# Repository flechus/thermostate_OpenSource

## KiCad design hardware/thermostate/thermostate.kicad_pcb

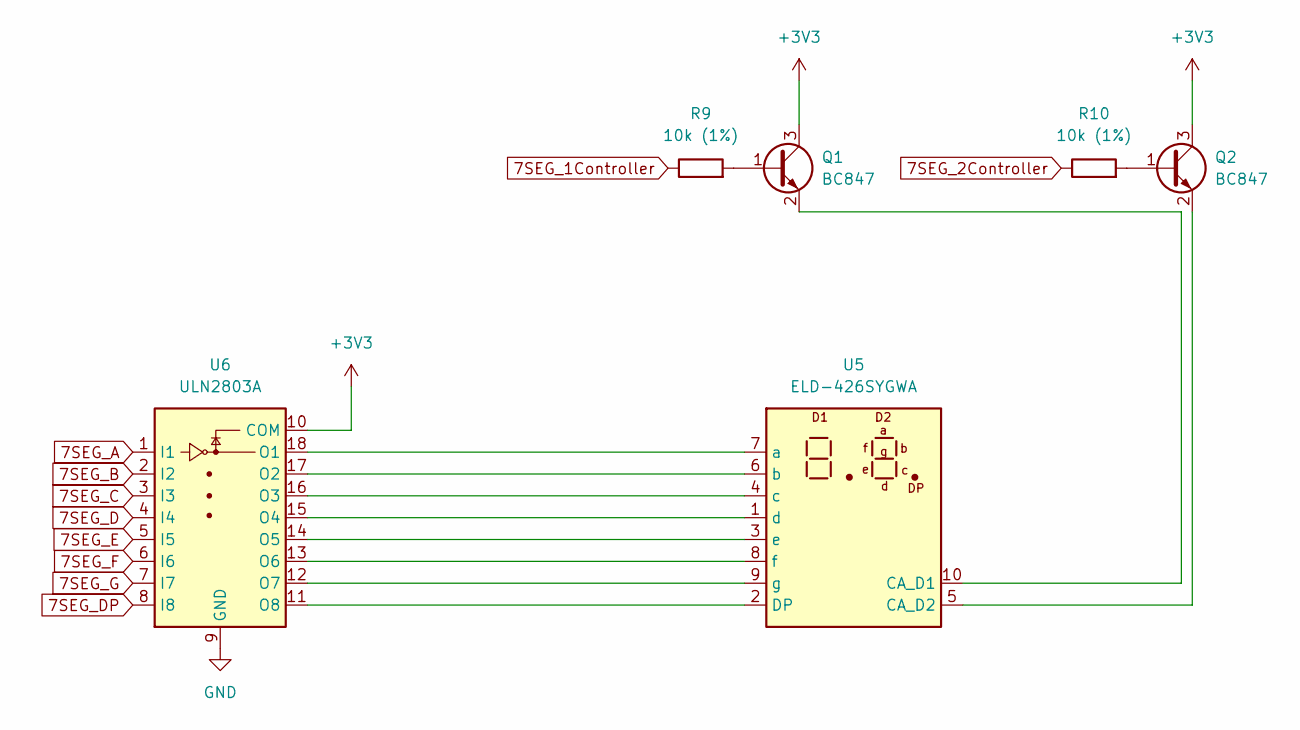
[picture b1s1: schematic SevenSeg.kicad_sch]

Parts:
Q1, Q2: BC847; SOT-23; LCSC Part# C181140
R9, R10: 10k (1%); R_0805_2012Metric_Pad1.20x1.40mm_HandSolder; LCSC Part# C17414
U5: ELD-426SYGWA; ELD_426XXXX
U6: ULN2803A; QFN-20-1EP_4x4mm_P0.5mm_EP2.5x2.5mm; LCSC Part# C493377

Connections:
7SEG_1Controller: R9.1; also elsewhere on the board
7SEG_2Controller: R10.1; also elsewhere on the board
7SEG_A: U6.1 (I1); also elsewhere on the board
7SEG_B: U6.2 (I2); also elsewhere on the board
7SEG_C: U6.3 (I3); also elsewhere on the board
7SEG_D: U6.4 (I4); also elsewhere on the board
7SEG_DP: U6.8 (I8); also elsewhere on the board
7SEG_E: U6.5 (I5); also elsewhere on the board
7SEG_F: U6.6 (I6); also elsewhere on the board
7SEG_G: U6.7 (I7); also elsewhere on the board
ESP_3V3: Q1.3 (C), Q2.3 (C), U6.10 (COM); also elsewhere on the board
GND: U6.9 (GND); also elsewhere on the board
unnamed: Q1.1 (B), R9.2
unnamed: Q1.2 (E), U5.10 (CA_D1)
unnamed: Q2.1 (B), R10.2
unnamed: Q2.2 (E), U5.5 (CA_D2)
unnamed: U5.1 (d), U6.15 (O4)
unnamed: U5.2 (DP), U6.11 (O8)
unnamed: U5.3 (e), U6.14 (O5)
unnamed: U5.4 (c), U6.16 (O3)
unnamed: U5.6 (b), U6.17 (O2)
unnamed: U5.7 (a), U6.18 (O1)
unnamed: U5.8 (f), U6.13 (O6)
unnamed: U5.9 (g), U6.12 (O7)

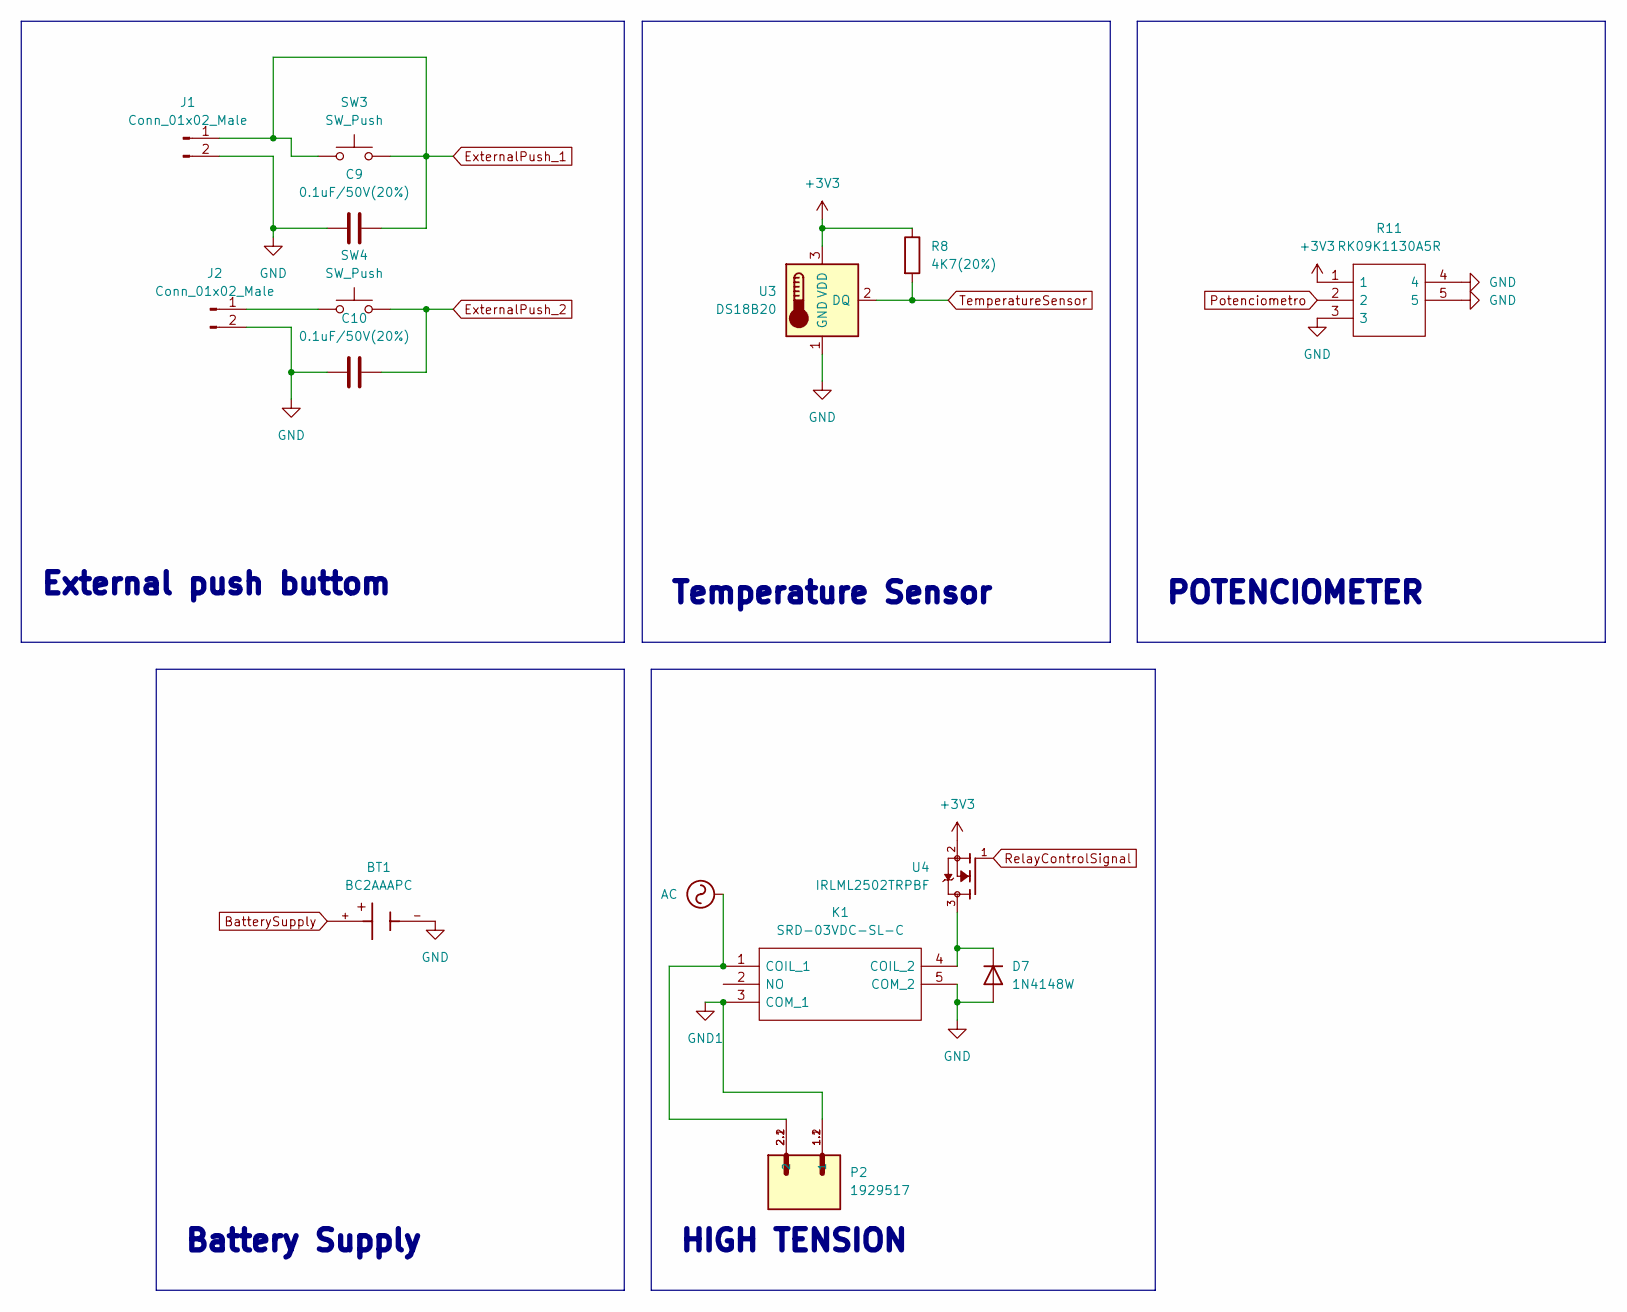
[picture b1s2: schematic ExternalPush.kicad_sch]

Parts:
BT1: BC2AAAPC; BAT_BC2AAAPC; PARTREV L
C9, C10: 0.1uF/50V(20%); C_0805_2012Metric_Pad1.18x1.45mm_HandSolder; LCSC Part# C138340
D7: 1N4148W; D_SOD-123
J1, J2: Conn_01x02_Male; TerminalBlock_MetzConnect_360291_1x01_Horizontal_ScrewM3.0_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
K1: SRD-03VDC-SL-C; SRD03VDCSLC; Manufacturer_Part_Number SRD-03VDC-SL-C; LCSC Part# C24585
P2: 1929517; PHOENIX_1929517
R8: 4K7(20%); R_0805_2012Metric_Pad1.20x1.40mm_HandSolder
R11: RK09K1130A5R; Manufacturer_Part_Number RK09K1130A5R; Mouser Part Number 688-RK09K1130A5R
SW3, SW4: SW_Push; SW_Push_1P1T_NO_CK_KMR2
U3: DS18B20; TO-92_Inline; LCSC Part# C9753
U4: IRLML2502TRPBF; SOT-23; LCSC Part# C2589

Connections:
AC: K1.1 (COIL_1), P2.2.1 (2), P2.2.2 (2)
BatterySupply: BT1.+; also elsewhere on the board
ESP_3V3: R8.1, R11.1, U3.3 (VDD), U4.2; also elsewhere on the board
ExternalPush_1: C9.2, J1.1, SW3.1, SW3.2; also elsewhere on the board
ExternalPush_2: C10.2, SW4.2; also elsewhere on the board
GND: BT1.-, C9.1, C10.1, D7.2 (A), J1.2, J2.2, K1.5 (COM_2), R11.3, R11.4, R11.5, U3.1 (GND); also elsewhere on the board
GND1: K1.3 (COM_1), P2.1.1 (1), P2.1.2 (1)
unnamed: D7.1 (K), K1.4 (COIL_2), U4.3
unnamed: J2.1, SW4.1
Potenciometro: R11.2; also elsewhere on the board
RelayControlSignal: U4.1; also elsewhere on the board
TemperatureSensor: R8.2, U3.2 (DQ); also elsewhere on the board

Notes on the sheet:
Battery Supply
POTENCIOMETER
HIGH TENSION
Temperature Sensor
External push buttom

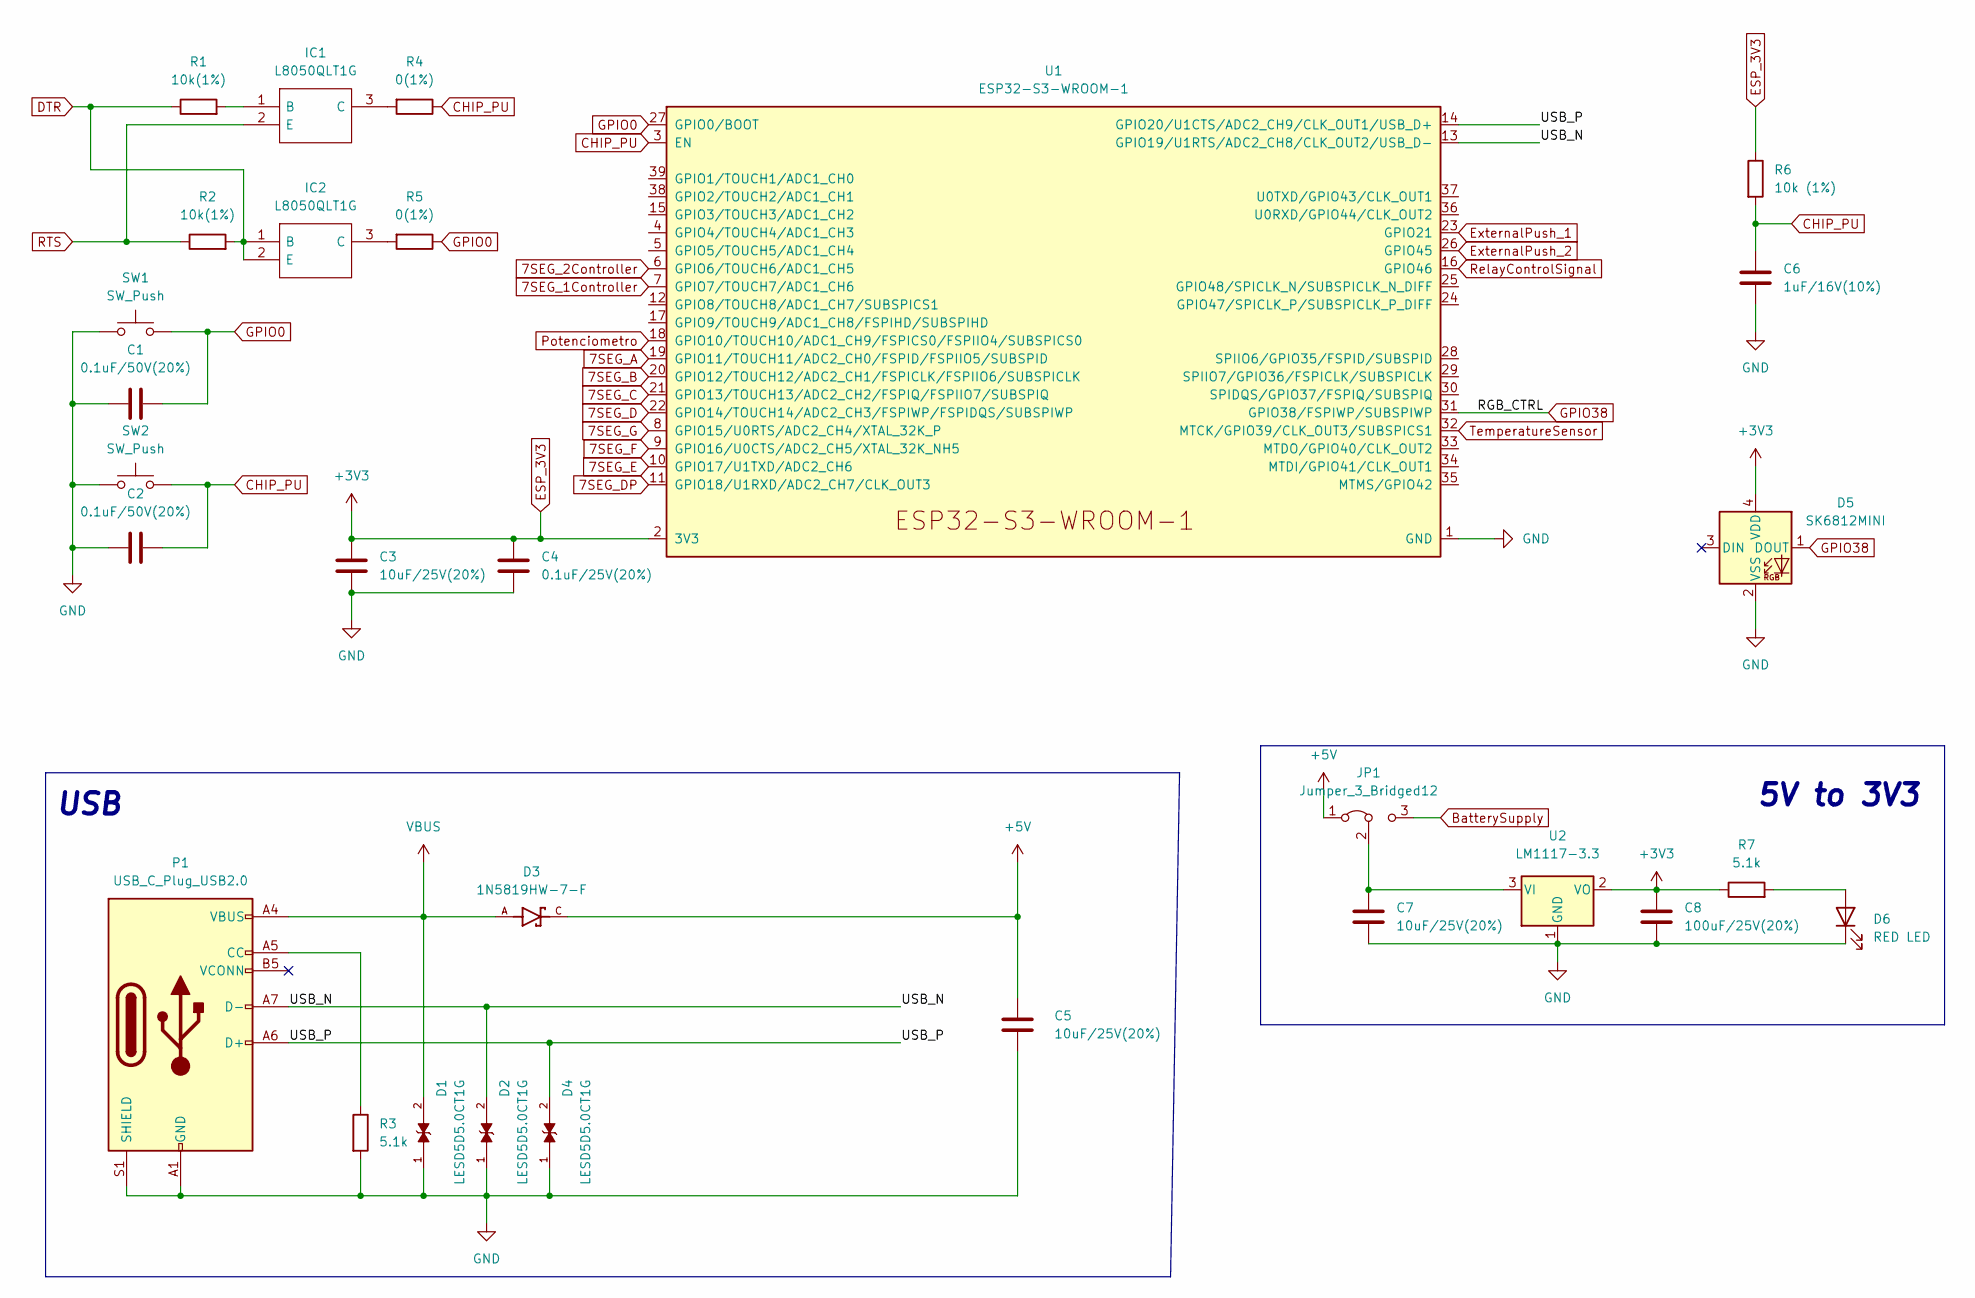
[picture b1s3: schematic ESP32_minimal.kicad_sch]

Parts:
C1, C2: 0.1uF/50V(20%); C_0805_2012Metric_Pad1.18x1.45mm_HandSolder; LCSC Part# C138340
C3, C5, C7: 10uF/25V(20%); C_0805_2012Metric_Pad1.18x1.45mm_HandSolder; LCSC Part# C669099
C4: 0.1uF/25V(20%); C_0805_2012Metric_Pad1.18x1.45mm_HandSolder; LCSC Part# C2180294
C6: 1uF/16V(10%); C_0805_2012Metric_Pad1.18x1.45mm_HandSolder; LCSC Part# C24123
C8: 100uF/25V(20%); C_0805_2012Metric_Pad1.18x1.45mm_HandSolder
D1, D2, D4: LESD5D5.0CT1G; D_SOD-523; PARTREV O; LCSC Part# C5199850
D3: 1N5819HW-7-F; D_SOD-123; PARTREV 18-2; LCSC Part# C82544
D5: SK6812MINI; LED_Kingbright_AAA3528ESGCT; LCSC Part# C2890038
D6: RED LED; LED_0805_2012Metric_Pad1.15x1.40mm_HandSolder; LCSC Part# C84256
IC1, IC2: L8050QLT1G; SOT-23_Handsoldering; Manufacturer_Part_Number L8050QLT1G; LCSC Part# C49581
JP1: Jumper_3_Bridged12; SolderJumper-3_P2.0mm_Open_TrianglePad1.0x1.5mm
P1: USB_C_Plug_USB2.0; USB_C_Receptacle_G-Switch_GT-USB-7010ASV; LCSC Part# C5299418
R1, R2: 10k(1%); R_0805_2012Metric_Pad1.20x1.40mm_HandSolder; LCSC Part# C269742
R3, R7: 5.1k; R_0805_2012Metric_Pad1.20x1.40mm_HandSolder; LCSC Part# C27834
R4, R5: 0(1%); R_0805_2012Metric_Pad1.20x1.40mm_HandSolder; LCSC Part# C17477
R6: 10k (1%); R_0805_2012Metric_Pad1.20x1.40mm_HandSolder; LCSC Part# C17414
SW1, SW2: SW_Push; SW_Push_1P1T_NO_CK_KMR2
U1: ESP32-S3-WROOM-1
U2: LM1117-3.3; SOT-23_Handsoldering

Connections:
7SEG_1Controller: U1.7 (GPIO7/TOUCH7/ADC1_CH6); also elsewhere on the board
7SEG_2Controller: U1.6 (GPIO6/TOUCH6/ADC1_CH5); also elsewhere on the board
7SEG_A: U1.19 (GPIO11/TOUCH11/ADC2_CH0/FSPID/FSPIIO5/S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); also elsewhere on the board
7SEG_B: U1.20 (GPIO12/TOUCH12/ADC2_CH1/FSPICLK/FSPIIO6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); also elsewhere on the board
7SEG_C: U1.21 (GPIO13/TOUCH13/ADC2_CH2/FSPIQ/FSPIIO7/S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); also elsewhere on the board
7SEG_D: U1.22 (GPIO14/TOUCH14/ADC2_CH3/FSPIWP/FSPIDQS/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); also elsewhere on the board
7SEG_DP: U1.11 (GPIO18/U1RXD/ADC2_CH7/CLK_OUT3); also elsewhere on the board
7SEG_E: U1.10 (GPIO17/U1TXD/ADC2_CH6); also elsewhere on the board
7SEG_F: U1.9 (GPIO16/U0CTS/ADC2_CH5/XTAL_32K_NH5); also elsewhere on the board
7SEG_G: U1.8 (GPIO15/U0RTS/ADC2_CH4/XTAL_32K_P); also elsewhere on the board
+5V: C5.1, D3.C, JP1.1 (A)
/ESP32_minimal/USB_N: D2.2, P1.A7 (D-), U1.13 (GPIO19/U1RTS/ADC2_CH8/CLK_OUT2/USB_D-)
/ESP32_minimal/USB_P: D4.2, P1.A6 (D+), U1.14 (GPIO20/U1CTS/ADC2_CH9/CLK_OUT1/USB_D+)
BatterySupply: JP1.3 (B); also elsewhere on the board
CHIP_PU: C2.2, C6.1, R4.1, R6.2, SW2.2, U1.3 (EN)
DTR: IC2.1 (B), IC2.2 (E), R1.1, R2.2
ESP_3V3: C3.1, C4.1, C8.1, D5.4 (VDD), R6.1, R7.1, U1.2 (3V3), U2.2 (VO); also elsewhere on the board
ExternalPush_1: U1.23 (GPIO21); also elsewhere on the board
ExternalPush_2: U1.26 (GPIO45); also elsewhere on the board
GND: C1.1, C2.1, C3.2, C4.2, C5.2, C6.2, C7.2, C8.2, D1.1, D2.1, D4.1, D5.2 (VSS), D6.1 (K), P1.A1 (GND), P1.A12 (GND), P1.B1 (GND), P1.B12 (GND), P1.S1 (SHIELD), R3.2, SW1.1, SW2.1, U1.1 (GND), U1.40 (GND), U1.41 (GND), U2.1 (GND); also elsewhere on the board
GPIO0: C1.2, R5.1, SW1.2, U1.27 (GPIO0/BOOT)
GPIO38: D5.1 (DOUT), U1.31 (GPIO38/FSPIWP/SUBSPIWP)
unnamed: C7.1, JP1.2 (C), U2.3 (VI)
unnamed: D6.2 (A), R7.2
unnamed: IC1.1 (B), R1.2
unnamed: IC1.3 (C), R4.2
unnamed: IC2.3 (C), R5.2
unnamed: P1.A5 (CC), R3.1
Potenciometro: U1.18 (GPIO10/TOUCH10/ADC1_CH9/FSPICS0/FSPIIO4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); also elsewhere on the board
RTS: IC1.2 (E), R2.1
RelayControlSignal: U1.16 (GPIO46); also elsewhere on the board
TemperatureSensor: U1.32 (MTCK/GPIO39/CLK_OUT3/SUBSPICS1); also elsewhere on the board
VBUS: D1.2, D3.A, P1.A4 (VBUS), P1.A9 (VBUS), P1.B4 (VBUS), P1.B9 (VBUS)

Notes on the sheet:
USB
5V to 3V3

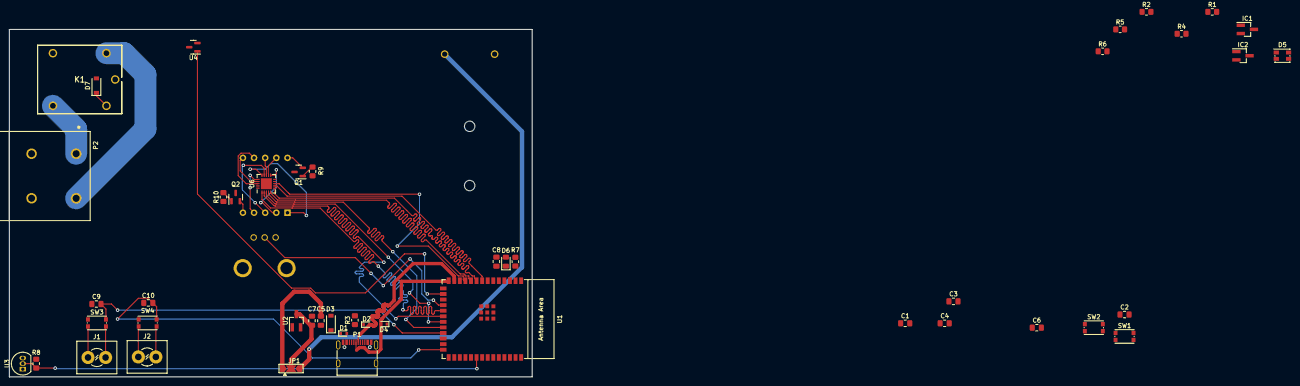
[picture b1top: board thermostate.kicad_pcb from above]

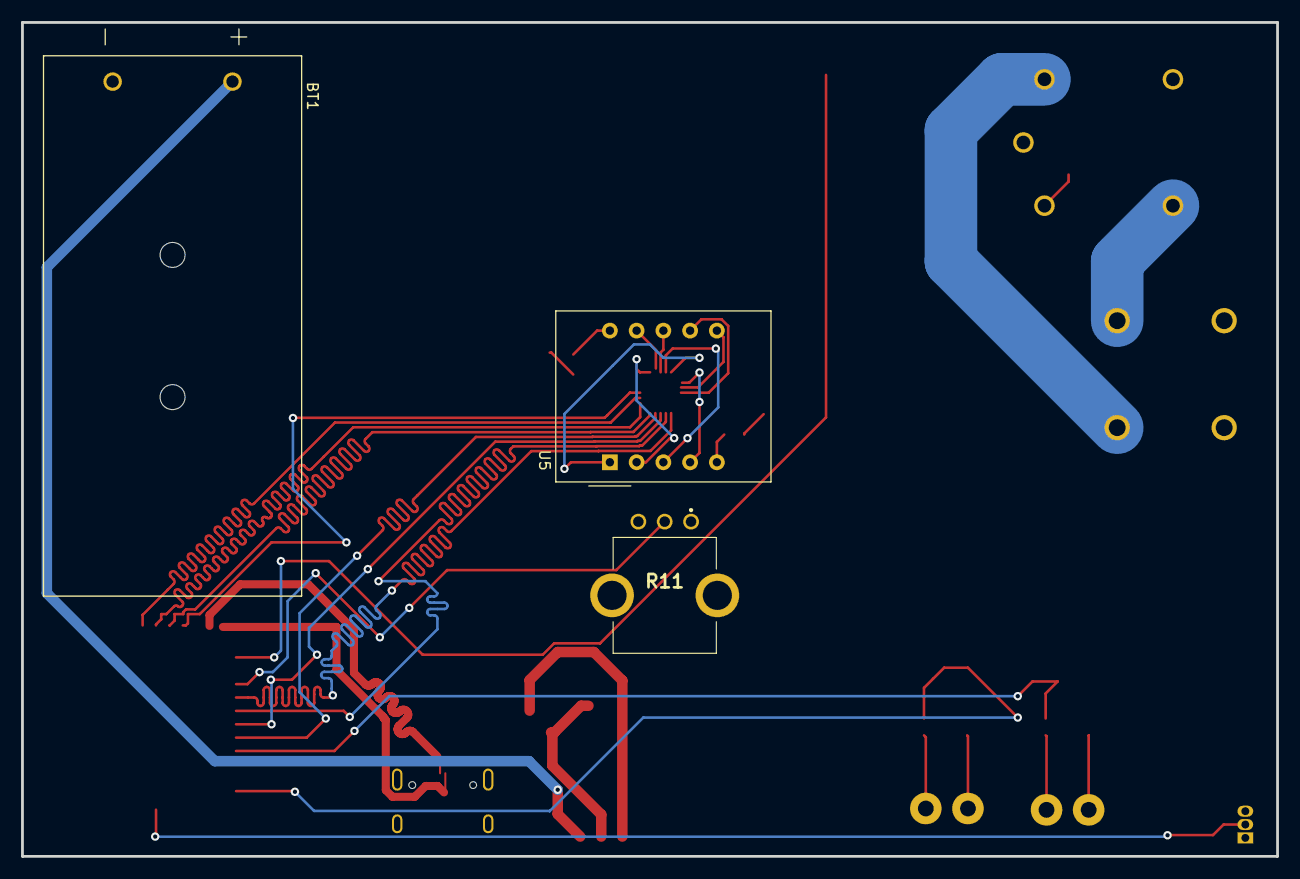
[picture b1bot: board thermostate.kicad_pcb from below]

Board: 4 copper layers, 119.2 x 79.2 mm, 49 parts (3 on the bottom side), 49 nets.

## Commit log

2023-02-07 Initial commit Add Hardware Folder
2023-02-07 Add Hardware Folder
2023-02-07 Add ESP32 kicad-libraries
2023-02-07 Add ESP32 SCH https://docs.espressif.com/projects/esp-idf/en/latest/esp32s3/hw-reference/esp32s3/user-guide-devkitc-1.html
2023-02-07 Add USB & 5V to 3V3 SCH
2023-02-07 Finnish ESP32 SCH, NOT revision
2023-02-11 Add LCSC row
2023-02-12 Add LCSC reference some components
2023-02-13 Add first PCB prototype
2023-02-17 Add temperature sensor
2023-02-19 Add Components PCB
2023-02-24 Add new elements
2023-02-24 Start desing PCB
2023-02-25 Add First lines PCB
2023-02-27 Add Battery Conector
2023-02-27 Add SCH with low power components
2023-03-04 Add Phoenix therminal and new mosfet
2023-03-04 New PCB desing
2023-03-17 Stop until next winter
